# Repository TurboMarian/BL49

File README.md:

# BL49
Wideband Lambda Controller with Bosch CJ125 and LSU 4.9 with 0-5V output and CAN-Bus Interface<br/>

### Suitable Bosch lambda probes: ###
|Bosch number  |Length overall|Comment|
|--------------|--------------|-------|
|0 258 017 025 |1000mm|Bosch motorsport part|
|0 258 017 012 |1060mm||
|0 281 004 184 |1000mm||
|0 281 004 150 |1215mm||
|0 258 017 126 |680mm|black, used by BMW after 09/2006 (1178 7561410)|
|0 258 017 029 |620mm|grey, used by BMW after 09/2006 (1178 7539124)|
|0 258 017 092 |950mm|black, used by BMW (1178 7540167)|
|0 258 017 038 |340mm|grey, used by BMW (11787537984)|
|...|||

**Probe pinout:**
|Pin#|Color|Description|Symbol|
|----|-----|--------|-----------|
|1|red|Pump current APE|IP|
|2|yellow|Virtual ground IPN|VM|
|3|white|Heater voltage H-|Uh-|
|4|grey|Heater voltaget H+|Uh+|
|5|green|Trim Resistor RT|IA|
|6|black|Nernst voltage UN|RE|

**Ua and Ur during calibration (cold sensor, 10 calibration samples with 10ms pause):**
- Ua: 359 => 1,7529V (should be 1.5V in calibration mode!)
- Ur: 337 => 1.6455V

**Changes:**
- 29.04.2020 - Version 0.0.1 -hardware released / software still in development, needs some changes in hardware<br/>
- 27.11.2021 - Version 0.0.3 - hardware in development, some modifications in analog PSU / software for V0.0.1 can be used with this<br/>

Interactive BOM for easier hand-soldering you can download from the github (BL49/hardware/V0.0.1/bom)
or access online here: https://oelprinz.000webhostapp.com/BL49/V0.0.1/iBOM/ibom.html <br/>
Quick link to schematic: https://github.com/oelprinz-org/BL49/blob/master/hardware/V0.0.1/schematics.pdf <br/>

<p align="center">
  
  <br/>

</p>

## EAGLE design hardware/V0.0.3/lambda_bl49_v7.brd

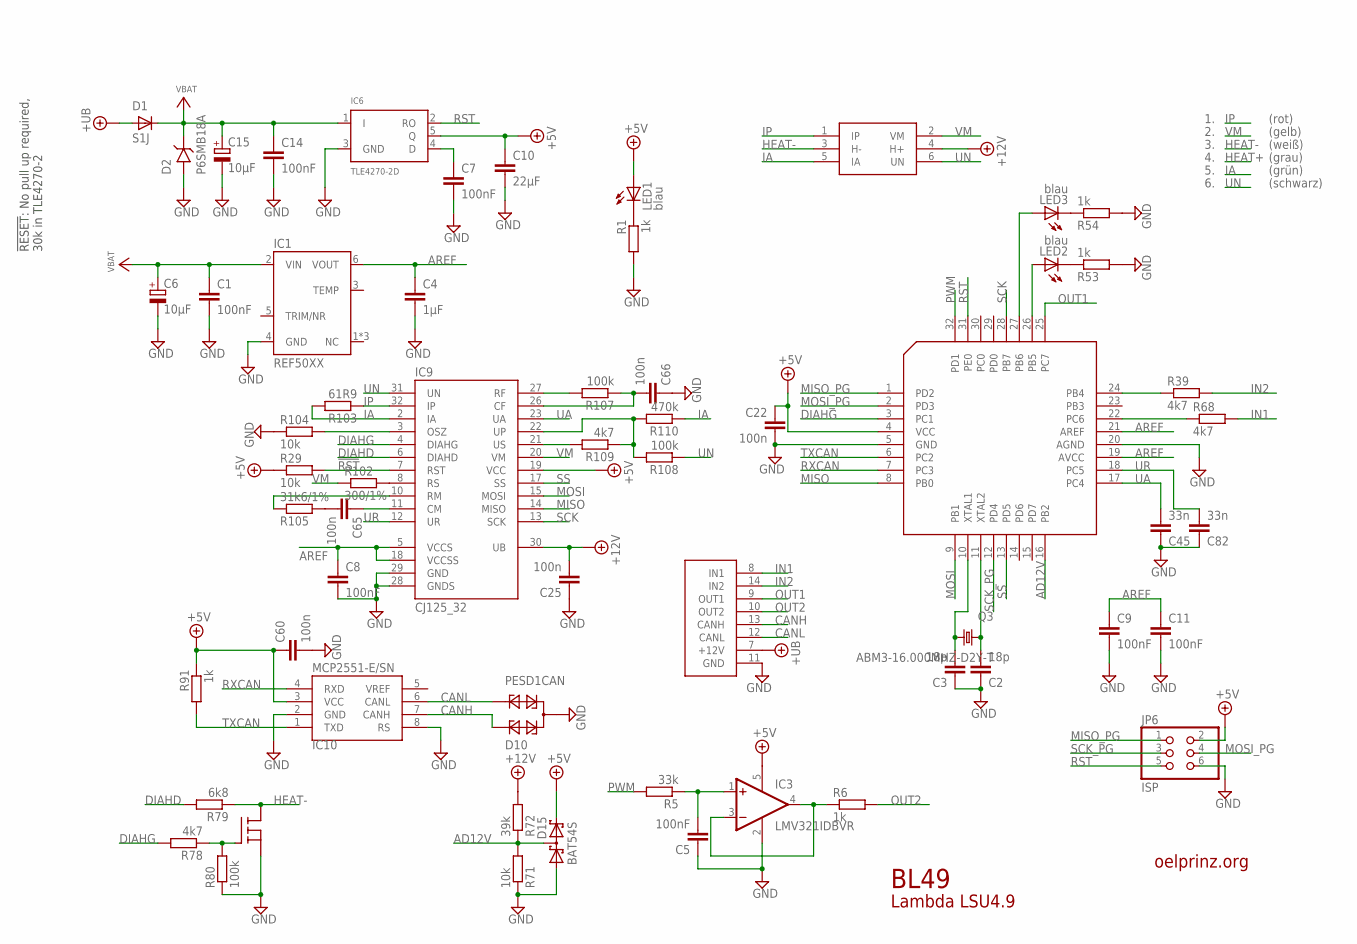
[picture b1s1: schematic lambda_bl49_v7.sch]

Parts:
C1, C5, C7, C8, C9, C11, C14: 100nF; C0603
C2, C3: 18p; C0603
C4: 1µF; C0603
C6, C15: 10µF; PANASONIC_D
C10: 22µF; C1206
C22, C25, C60, C65, C66: 100n; C0603
C45, C82: 33n; C0603
D1: S1J; SMADIODE
D2: P6SMB18A; DO-214AA
D10: PESD1CAN; SOT23
D15: BAT54S; SOT23
IC1: REF50XX; SOIC127P600X175-8N
IC3: LMV321IDBVR; SC70-5L
IC6: TLE4270-2D; TO252-51
IC9: CJ125_32; TQFP32-08
IC10: MCP2551-E/SN; SOIC8
JP6: ISP; 2X03
LED1, LED2, LED3: blau; SML0805
Q3: ABM3-16.000MHZ-D2Y-T; ABM3
R1, R6, R53, R54, R91: 1k; R0603
R5: 33k; R0603
R29, R71, R104: 10k; R0603
R39, R68, R78, R109: 4k7; R0603
R72: 39k; R0603
R79: 6k8; R0603
R80, R107, R108: 100k; R0603
R102: 300/1%; R0603
R103: 61R9; R0603
R105: 31k6/1%; R0603
R110: 470k; R0603
U$1: BL49
U$2: ATMEGA32M1-AU; TQFP32-08
U$3: STD30NF06LT4; DPACK_2

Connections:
!RST: IC9.7 (RST), R29.2
+5V: C10.1, C22.1, C60.1, D15.2 (C2), IC3.5 (V+), IC6.5 (Q), IC9.19 (VCC), IC10.3 (VCC), JP6.2, LED1.A, R29.1, R91.1, U$2.4 (VCC)
+12V: C25.2, IC9.30 (UB), R72.2, U$1.4 (H+)
+UB: D1.A, U$1.7 (+12V)
AD12V: D15.3 (C1A2), R71.2, R72.1, U$2.16 (PB2)
AREF: C4.1, C8.1, C9.1, C11.1, IC1.6 (VOUT), IC9.5 (VCCS), IC9.18 (VCCSS), U$2.19 (AVCC), U$2.21 (AREF)
CANH: D10.1, IC10.7 (CANH), U$1.13 (CANH)
CANL: D10.2, IC10.6 (CANL), U$1.12 (CANL)
DIAHD: IC9.6 (DIAHD), R79.2
DIAHG: IC9.4 (DIAHG), R78.2, U$2.3 (PC1)
GND: C1.2, C2.1, C3.1, C4.2, C5.1, C6.-, C7.2, C8.2, C9.2, C10.2, C11.2, C14.2, C15.-, C22.2, C25.1, C45.1, C60.2, C66.1, C82.1, D2.P$2 (A), D10.3, D15.1 (A1), IC1.4 (GND), IC3.2 (V-), IC6.3 (GND), IC9.28 (GNDS), IC9.29 (GND), IC10.2 (GND), IC10.8 (RS), JP6.6, R1.2, R53.2, R54.2, R71.1, R80.1, R104.1, U$1.11 (GND), U$2.5 (GND), U$2.20 (AGND), U$3.S (3)
HEAT-: R79.1, U$1.3 (H-), U$3.D (2)
IA: IC9.2 (IA), R103.2, R110.1, U$1.5 (IA)
IN1: R68.2, U$1.8 (IN1)
IN2: R39.2, U$1.14 (IN2)
IP: IC9.32 (IP), R103.1, U$1.1 (IP)
MISO: IC9.14 (MISO), U$2.8 (PB0)
MISO_PG: JP6.1, U$2.1 (PD2)
MOSI: IC9.15 (MOSI), U$2.9 (PB1)
MOSI_PG: JP6.4, U$2.2 (PD3)
unnamed: IC9.3 (OSZ), R104.2
unnamed: LED1.C, R1.1
unnamed: C7.1, IC6.4 (D)
unnamed: IC9.10 (RM), R105.1
unnamed: C5.2, IC3.1 (+IN), R5.1
unnamed: IC3.3 (-IN), IC3.4 (OUT), R6.1
unnamed: C2.2, Q3.1, U$2.11 (XTAL2)
unnamed: C65.1, IC9.11 (CM)
unnamed: C3.2, Q3.2, U$2.10 (XTAL1)
unnamed: C65.2, R105.2
unnamed: IC9.8 (RS), R102.2
unnamed: R39.1, U$2.24 (PB4)
unnamed: LED2.A, U$2.26 (PB5)
unnamed: LED2.C, R53.1
unnamed: LED3.C, R54.1
unnamed: LED3.A, U$2.27 (PB6)
unnamed: R68.1, U$2.22 (PC6)
unnamed: IC9.27 (RF), R107.2
unnamed: IC9.22 (UP), R108.2, R109.1, R110.2
unnamed: IC9.21 (US), R109.2
unnamed: R78.1, R80.2, U$3.G (1)
unnamed: C66.2, IC9.26 (CF), R107.1
OUT1: U$1.9 (OUT1), U$2.25 (PC7)
OUT2: R6.2, U$1.10 (OUT2)
PWM: R5.2, U$2.32 (PD1)
RST: IC6.2 (RO), JP6.5, U$2.31 (PE0)
RXCAN: IC10.4 (RXD), U$2.7 (PC3)
SCK: IC9.13 (SCK), U$2.28 (PB7)
SCK_PG: JP6.3, U$2.12 (PD4)
SS: IC9.17 (SS), U$2.13 (PD5)
TXCAN: IC10.1 (TXD), R91.2, U$2.6 (PC2)
UA: C45.2, IC9.23 (UA), U$2.17 (PC4)
UN: IC9.31 (UN), R108.1, U$1.6 (UN)
UR: C82.2, IC9.12 (UR), U$2.18 (PC5)
VBAT: C1.1, C6.+, C14.1, C15.+, D1.C, D2.P$1 (C), IC1.2 (VIN), IC6.1 (I)
VM: IC9.20 (VM), R102.1, U$1.2 (VM)

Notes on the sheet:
Lambda LSU4.9
oelprinz.org
BL49
(grau)
(weiß)
(gelb)
(grün)
(rot)
(schwarz)
!RESET!: No pull up required, 30k in TLE4270-2

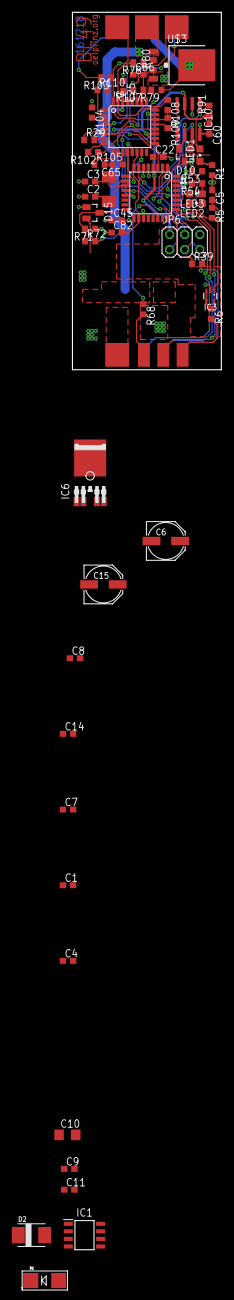
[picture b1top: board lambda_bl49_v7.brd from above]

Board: 2 copper layers, 25.0 x 60.0 mm, 59 parts (0 on the bottom side), 56 nets.

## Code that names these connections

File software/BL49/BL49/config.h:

/*
 * config.h
 *
 * Created: 16.10.2021 15:10:09
 *  Author: Heinrich
 */ 


#ifndef CONFIG_H_
#define CONFIG_H_

#include <avr/io.h>
#include <avr/interrupt.h>

#ifndef F_CPU
#warning "F_CPU war noch nicht definiert, wird nun mit 16MHz definiert"
#define F_CPU 16000000     /* Quarz mit 16 Mhz */
#endif

#ifndef FOSC
#warning "FOSC war noch nicht definiert, wird nun mit F_CPU/1000 definiert"
#define FOSC	F_CPU/1000
#endif

#ifndef CAN_BAUDRATE
#warning "CAN_BAUDRATE war noch nicht definiert, wird nun mit 500kbit definiert"
#define CAN_BAUDRATE	500
#endif

#define CAN_ID		0x180
#define CAN_DLC		8

// leds
#define LEDS			DDRB
#define LEDS_PORT		PORTB
#define CPC1017			PB3
#define LED2			PB5
#define LED3			PB6
#define CPC1017_ON		(LEDS_PORT |= (1 << CPC1017))
#define CPC1017_OFF		(LEDS_PORT &= ~(1 << CPC1017))
#define LED2_ON			(LEDS_PORT |= (1 << LED2))
#define LED2_OFF		(LEDS_PORT &= ~(1 << LED2))
#define LED2_TOG		(LEDS_PORT ^= (1 << LED2))
#define LED3_ON			(LEDS_PORT |= (1 << LED3))
#define LED3_OFF		(LEDS_PORT &= ~(1 << LED3))
#define LED3_TOG		(LEDS_PORT ^= (1 << LED3))

// spi
#define SPI_MOSI		PB1
#define SPI_SCK			PB7
#define SPI_SS			PD5
#define SPI_SS_SELECT	(PORTD &= ~(1 << SPI_SS))
#define SPI_SS_DESELECT	(PORTD |= (1 << SPI_SS))

// checks for adc
#define UBat_MIN		0x01C4	// 10,8V; 0x01C4 => 452 => 10,81V
#define UBat_MAX		0x02B0	// 16,5V; 0x02B0 => 688 => 16,46V

// heater
#define	HEATER_PIN		PC1
#define HEATER_PORT		PORTC
#define HEATER_ON		(HEATER_PORT &= ~(1 << HEATER_PIN))
#define HEATER_OFF		(HEATER_PORT |= (1 << HEATER_PIN))
#define HEATER_TOG		(HEATER_PORT ^= (1 << HEATER_PIN))
#define HEATER_MAX_V	0x021F	// 13V

#endif /* CONFIG_H_ */

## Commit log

2021-10-16 software initial import
2021-10-17 .gitignore added
2021-10-17 cleaned project
2021-10-17 got can running
2021-10-18 aemnet datasheet added, some can stuff
2021-10-19 aemnet AEM X-Series protocoll implemented
2021-10-19 some adc functions added
2021-10-27 dac stuff added, spi stuff added
2021-10-28 pwm stuff added
2021-10-28 spi implemented, adc corrected, some pins/ports corrected, cj125 basic communication implemented
2021-10-29 adc input reading corrected
2021-10-29 adc and pwm corrected
2021-10-31 -> new datasheet added -> start pwm duty set to 0 -> lsu 4.9 pin out added
2021-10-31 Update README.md
    Bosch probe number and pinout added
2021-11-01 added schematic of my pcb... added probe condensing and preheating
2021-11-12 revision V0.0.3 created and added some datasheets
2021-11-13 eagle v7 schematic added
2021-11-27 tls115 replaced by ti ref5050
2021-12-04 description modified
2021-12-05 pid added
2021-12-06 bosch probe list added

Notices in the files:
parts and their libraries:
microbuilder: This work is placed in the public domain, and may be freely used for commercial and non-commercial work with the following conditions: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
